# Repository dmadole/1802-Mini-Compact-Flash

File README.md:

# 1802-Mini-Compact-Flash
This is the compact flash card for the [1802/Mini](https://github.com/dmadole/1802-Mini) system. It supports the following features:

* Has on-board compact flash socket, no adapters are needed
* Software compatible with Mike Riley's IDE interface design
* Runs Elf/OS using standard Pico/Elf ROMs and software
* Jumper selectable for I/O ports 2 & 3, 4 & 5, or 6 & 7
* Jumper selectable interrupt flag or status signal to EF1-4
* I/O group selection in system equipped with expander card
* Supports DMA operation with 10x accelerated transfer rate
* Supports interrupt-driven operation for multi-tasking OS
* Compact flash completely buffer-isolated from expansion bus
* Activity indicator LED provided as driven by CF card
* Highly annotated silkscreen documents settings and pins
* Creates probably the fastest Elf/OS system in the world

Gerber files for the PCBs and PDF schematics can be found in [Releases](https://github.com/dmadole/1802-Mini-Compact-Flash/releases).

BOMS and any applicable errata or other notes can be found in [notes](https://github.com/dmadole/1802-Mini-Compact-Flash/tree/main/notes).

For availability of kits and bare PCBs please see http://madole.net/1802/mini/kits

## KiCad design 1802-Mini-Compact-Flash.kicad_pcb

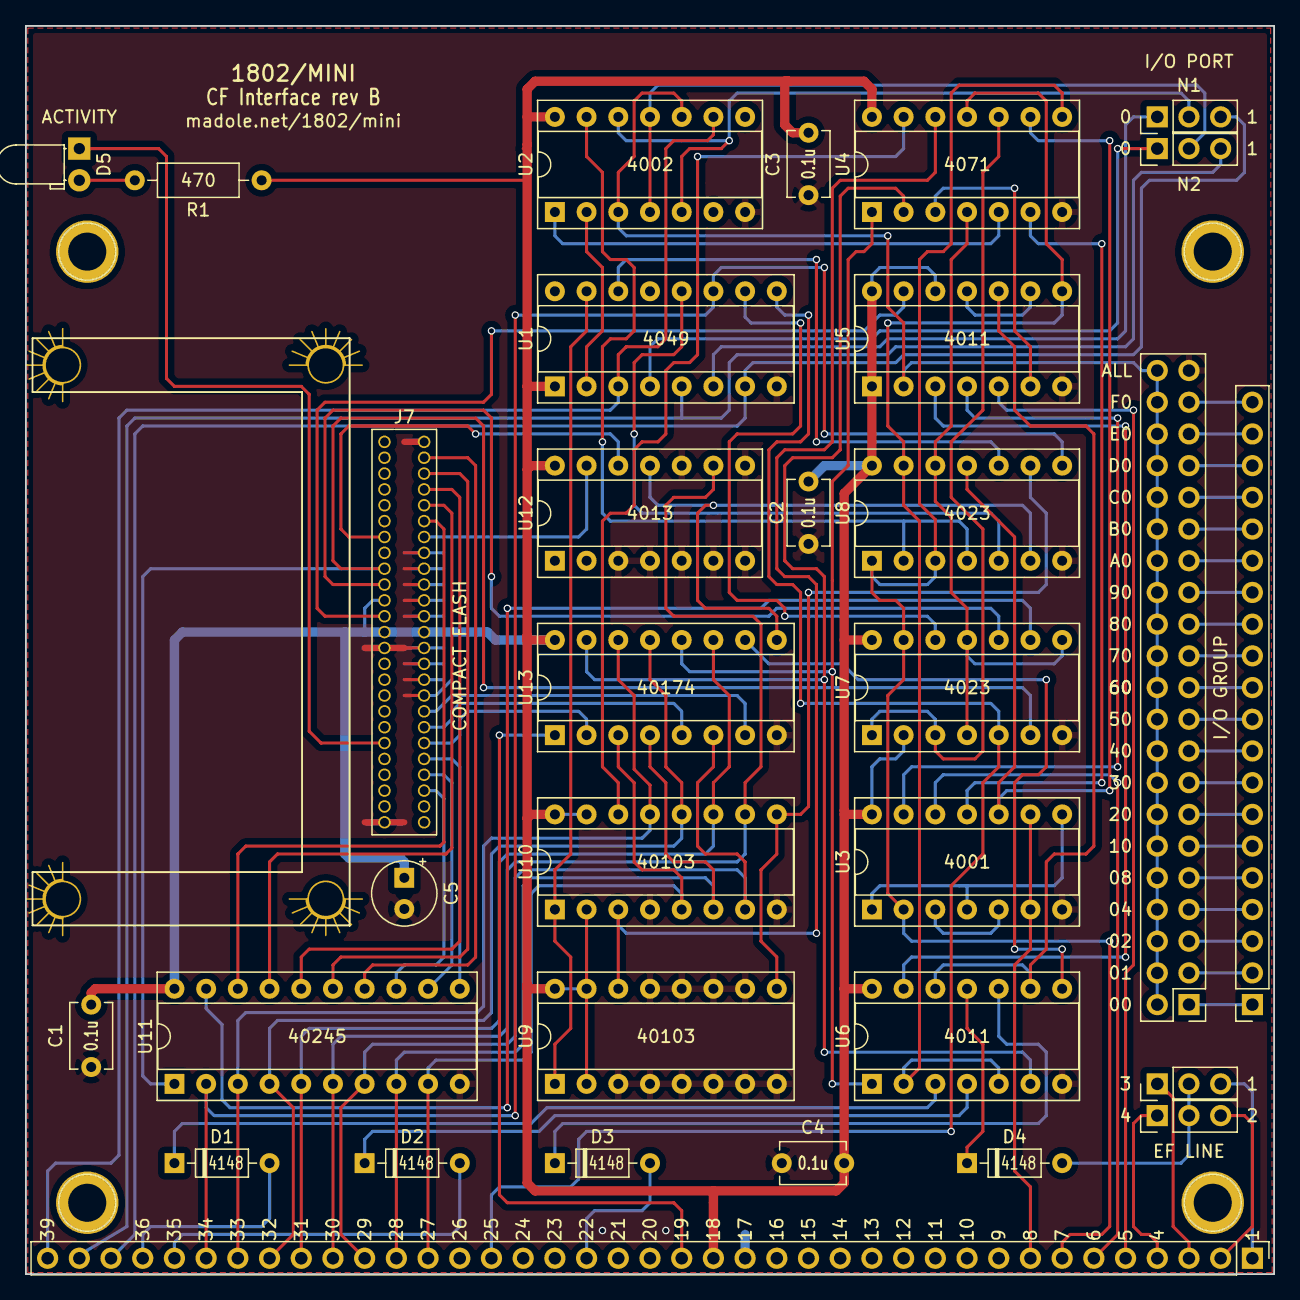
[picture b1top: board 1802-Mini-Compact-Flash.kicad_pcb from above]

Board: 2 copper layers, 100.0 x 100.0 mm, 36 parts (0 on the bottom side), 101 nets.

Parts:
C1, C2, C3, C4: 0.1u; C_Disc_D5.1mm_W3.2mm_P5.00mm
C5: 10u; CP_Radial_Tantal_D5.0mm_P2.50mm
D1, D2, D3, D4: 4148; D_DO-35_SOD27_P7.62mm_Horizontal
D5: LED; LED_D3.0mm_Horizontal_O1.27mm_Z2.0mm
J1, J2, J3, J4: Mount; 1pin
J5: Expansion; Pin_Header_Straight_1x39_Pitch2.54mm
J6: Conn_01x20; PinSocket_1x20_P2.54mm_Vertical
J7: CF; samtec
J8: Conn_02x21_Odd_Even; PinHeader_2x21_P2.54mm_Vertical
JP1, JP2, JP3, JP4: Jumper_3_Bridged12; PinHeader_1x03_P2.54mm_Vertical
R1: 470; R_Axial_DIN0207_L6.3mm_D2.5mm_P10.16mm_Horizontal
U1: 4049; DIP-16_W7.62mm_Socket
U2: 4002; DIP-14_W7.62mm_Socket
U3: 4001; DIP-14_W7.62mm_Socket
U4: 4071; DIP-14_W7.62mm_Socket
U5, U6: 4011; DIP-14_W7.62mm_Socket
U7, U8: 4023; DIP-14_W7.62mm_Socket
U9, U10: 40103; DIP-16_W7.62mm_Socket
U11: 40245; DIP-20_W7.62mm_Socket
U12: 4013; DIP-14_W7.62mm_Socket
U13: 40174; DIP-16_W7.62mm_Socket

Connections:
/A0: J7.20, U13.2
/A1: J7.19, U13.5
/A2: J7.18, U13.7
/BUS0: J5.27, U10.5, U11.9, U13.3
/BUS1: J5.28, U10.6, U11.8, U13.4
/BUS2: J5.29, U10.7, U11.7, U13.6
/BUS3: J5.30, U10.10, U11.6, U12.9
/BUS4: J5.31, U10.11, U11.5, U13.11
/BUS5: J5.32, U10.12, U11.4, U13.13
/BUS6: J5.33, U10.13, U11.3, U13.14
/D00: J7.21, U11.11
/D01: J7.22, U11.12
/D02: J7.23, U11.13
/D03: J7.2, U11.14
/D04: J7.3, U11.15
/D05: J7.4, U11.16
/D06: J7.5, U11.17
/D07: J7.6, U11.18
/INTRQ: J7.37, U5.13
/~CS0: J7.7, U12.13
/~CS1: J7.32, U12.12
/~DASP: D5.1, J7.45
BUS7: J5.34, U1.11, U8.8, U11.2
CLK: U3.10, U4.9, U8.11
DMA: U3.11, U4.6
DMAIN_EN: U4.1, U6.1, U13.12
DMAOUT_EN: U4.2, U6.6, U13.15
GND: C1.2, C2.2, C3.2, C4.2, C5.2, J5.17, J7.1, J7.8, J7.9, J7.10, J7.11, J7.12, J7.14, J7.15, J7.16, J7.17, J7.39, J7.50, J8.41, U1.8, U2.7, U3.7, U4.7, U5.7, U6.7, U7.7, U8.7, U9.3, U9.4, U9.5, U9.6, U9.7, U9.8, U9.10, U9.11, U9.12, U9.13, U10.4, U10.8, U11.10, U12.3, U12.4, U12.5, U12.6, U12.7, U12.8, U12.10, U13.8
GROUP: U5.3, U6.13
INP: U4.10, U7.1, U7.3
INT_EN: U6.8, U13.10
IO: U4.4, U7.4, U7.8, U7.11, U8.12
N0: J5.39, U1.3, U2.9
N1: J5.38, JP1.3, U1.5
N2: J5.37, JP2.3, U1.7
unnamed: D1.1, U6.3
unnamed: D2.1, U6.4
unnamed: D3.1, U6.10
unnamed: D4.1, U6.11
unnamed: D4.2, JP3.2, JP4.2
unnamed: D5.2, R1.2
unnamed: J6.1, J8.1
unnamed: J6.2, J8.3
unnamed: J6.3, J8.5
unnamed: J6.4, J8.7
unnamed: J6.5, J8.9
unnamed: J6.6, J8.11
unnamed: J6.7, J8.13
unnamed: J6.8, J8.15
unnamed: J6.9, J8.17
unnamed: J6.10, J8.19
unnamed: J6.11, J8.21
unnamed: J6.12, J8.23
unnamed: J6.13, J8.25
unnamed: J6.14, J8.27
unnamed: J6.15, J8.29
unnamed: J6.16, J8.31
unnamed: J6.17, J8.33
unnamed: J6.18, J8.35
unnamed: J6.19, J8.37
unnamed: J6.20, J8.39
unnamed: JP1.1, U1.4
unnamed: JP1.2, U2.4, U2.11
unnamed: JP2.1, U1.6
unnamed: JP2.2, U2.5, U2.12
unnamed: U1.2, U2.2
unnamed: U1.10, U7.12
unnamed: U1.12, U8.5
unnamed: U1.14, U8.10
unnamed: U1.15, U9.1, U10.1
unnamed: U3.1, U3.4, U3.8
unnamed: U3.3, U3.5
unnamed: U3.13, U5.4
unnamed: U4.3, U5.6
unnamed: U5.10, U6.9, U6.12
unnamed: U4.12, U9.14, U10.3
unnamed: U4.13, U10.14
PORT2: U2.13, U8.2, U8.4
PORT3: U2.1, U4.5
SC0: J5.6, U3.12
SC1: J5.5, U5.5
TPA: J5.8, U3.6, U3.9
TPB: J5.7, U3.2, U4.8, U7.13, U8.1, U8.3
VCC: C1.1, C2.1, C3.1, C4.1, C5.1, J5.18, J7.13, J7.36, J7.38, R1.1, U1.1, U2.14, U3.14, U4.14, U5.1, U5.12, U5.14, U6.14, U7.2, U7.14, U8.14, U9.2, U9.15, U9.16, U10.2, U10.15, U10.16, U11.20, U12.14, U13.16
~CLEAR: J5.19, U13.1
~CTL_LE: U8.6, U12.11, U13.9
~CTR_LE: U8.9, U9.9, U10.9
~DATA: U7.9, U11.19
~DMAIN: D1.2, J5.36
~DMAOUT: D2.2, J5.35
~EF1: J5.1, JP3.3
~EF2: J5.2, JP4.3
~EF3: J5.3, JP3.1
~EF4: J5.4, JP4.1
~GROUP: J8.2, J8.4, J8.6, J8.8, J8.10, J8.12, J8.14, J8.16, J8.18, J8.20, J8.22, J8.24, J8.26, J8.28, J8.30, J8.32, J8.34, J8.36, J8.38, J8.40, J8.42, U2.3, U2.10, U5.2
~INTERRUPT: D3.2, J5.22
~INTRQ: U5.9, U5.11
~IORD: J7.34, U7.6, U11.1
~IOWR: J7.35, U7.10
~MRD: J5.25, U1.9, U7.5
~ZERO: U4.11, U5.8, U6.2, U6.5, U8.13

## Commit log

2021-06-23 Add BOM
2021-06-27 Added notes and references to BOM
2021-06-28 Correct mfr part no of single row header
2022-08-07 Add group jumper to image
